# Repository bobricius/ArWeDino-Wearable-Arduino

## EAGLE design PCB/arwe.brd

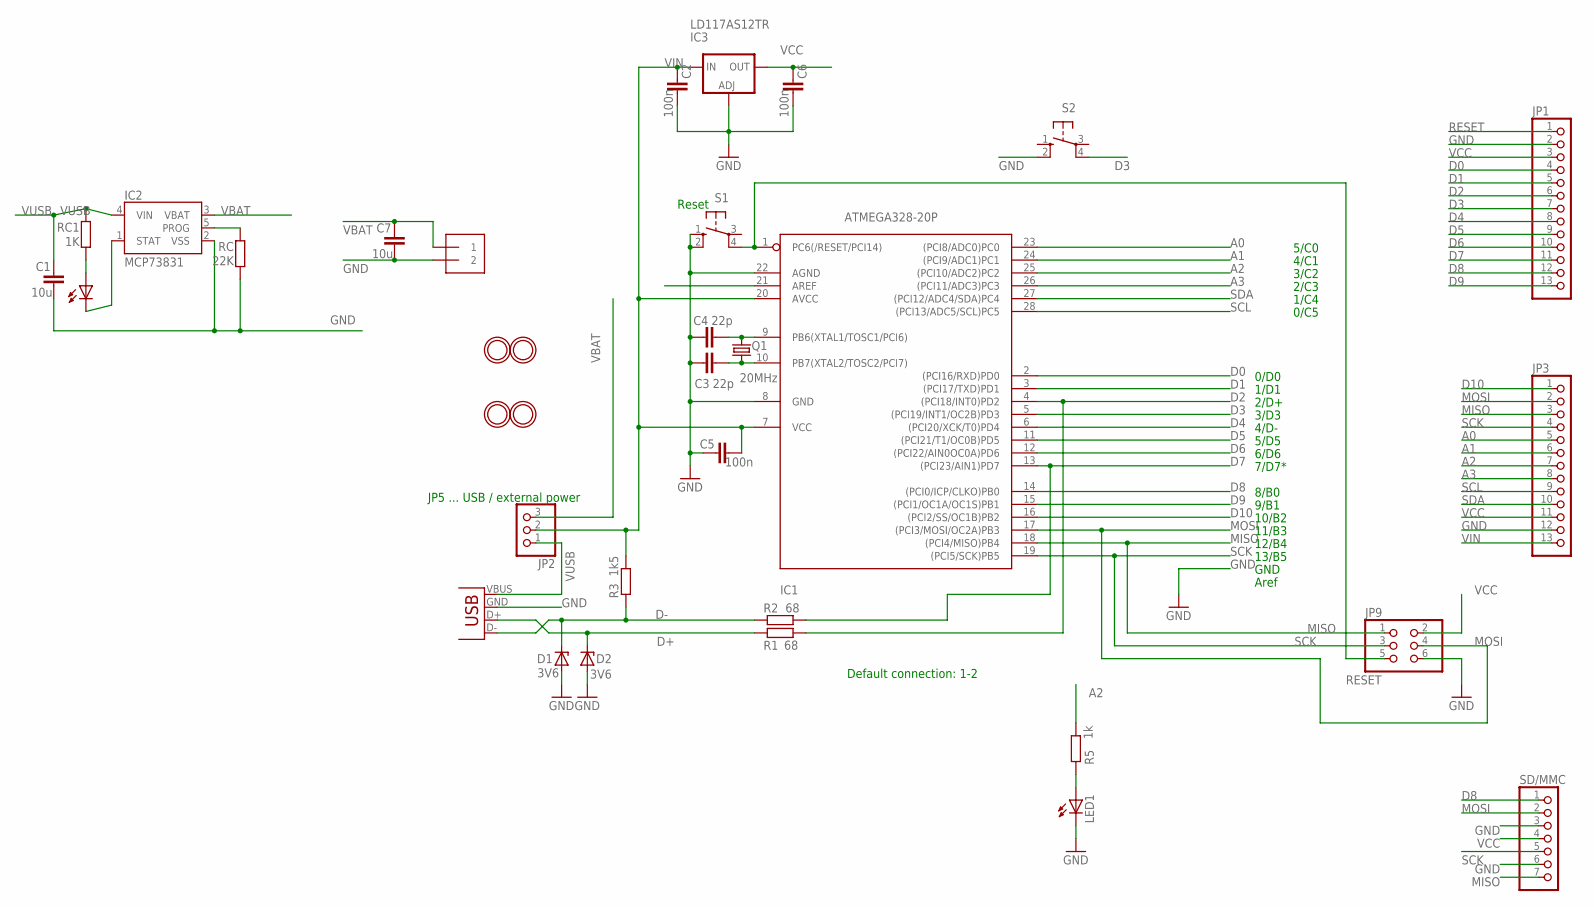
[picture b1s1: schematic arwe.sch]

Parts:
C1, C7: 10u; C0603
C2, C5, C6: 100n; C025-024X044
C3, C4: 22p; C025-024X044
CHG: 0805; CHIPLED_0603
D1, D2: 3V6; ZDIO-5
IC1: ATMEGA328-20P; DIL28-3
IC2: MCP73831; SOT23-5
IC3: LD117AS12TR; SOT223
J1: 1X2-3.5MM
JP1, JP3: PINHD-1X13; 1X13
JP2: PINHD-1X3; 1X03
JP9: PINHD-2X3; 2X03
LED1: LED3MM
Q1: 20MHz; HC49/S
R1, R2: 68; 0204/5
R3: 1k5; 0204/5
R5: 1k; 0204/5
RC: 22K; R0603
RC1: 1K; R0603
S1: 10-XX; B3F-10XX
S2: 10-XX; B3F-10XX; MPN B3F-1000
SD/MMC: PINHD-1X7; 1X07
U$2, U$3, U$4, U$5: MOUNTINGHOLE3.0THIN; MOUNTINGHOLE_3.0_PLATEDTHIN
X1: USB-A-H

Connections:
A0: IC1.23 ((PCI8/ADC0)PC0), JP3.5
A1: IC1.24 ((PCI9/ADC1)PC1), JP3.6
A2: IC1.25 ((PCI10/ADC2)PC2), JP3.7, R5.1
A3: IC1.26 ((PCI11/ADC3)PC3), JP3.8
AREF_RAW: IC1.21 (AREF)
D0: IC1.2 ((PCI16/RXD)PD0), JP1.4
D1: IC1.3 ((PCI17/TXD)PD1), JP1.5
D2: IC1.4 ((PCI18/INT0)PD2), JP1.6, R1.2
D3: IC1.5 ((PCI19/INT1/OC2B)PD3), JP1.7, S2.4 (P1)
D4: IC1.6 ((PCI20/XCK/T0)PD4), JP1.8
D5: IC1.11 ((PCI21/T1/OC0B)PD5), JP1.9
D6: IC1.12 ((PCI22/AIN0OC0A)PD6), JP1.10
D7: IC1.13 ((PCI23/AIN1)PD7), JP1.11, R2.2
D8: IC1.14 ((PCI0/ICP/CLKO)PB0), JP1.12, SD/MMC.1
D9: IC1.15 ((PCI1/OC1A/OC1S)PB1), JP1.13
D10: IC1.16 ((PCI2/SS/OC1B)PB2), JP3.1
D+: D2.C, R1.1, X1.D+ (D-)
D-: D1.C, R2.1, R3.1, X1.D- (D+)
GND: C1.2, C2.2, C3.1, C4.1, C5.1, C6.2, C7.2, D1.A, D2.A, IC1.8 (GND), IC1.22 (AGND), IC2.2 (VSS), IC3.1 (ADJ), J1.2, JP1.2, JP3.12, JP9.6, LED1.K (C), RC.1, S1.1 (S), S1.2 (S1), S2.2 (S1), SD/MMC.3, SD/MMC.6, X1.GND (VBUS)
MISO: IC1.18 ((PCI4/MISO)PB4), JP3.3, JP9.1, SD/MMC.7
MOSI: IC1.17 ((PCI3/MOSI/OC2A)PB3), JP3.2, JP9.4, SD/MMC.2
unnamed: LED1.A, R5.2
unnamed: CHG.A, RC1.1
unnamed: CHG.C, IC2.1 (STAT)
unnamed: IC2.5 (PROG), RC.2
unnamed: C3.2, IC1.10 (PB7(XTAL2/TOSC2/PCI7)), Q1.1
unnamed: C4.2, IC1.9 (PB6(XTAL1/TOSC1/PCI6)), Q1.2
RESET: IC1.1 (PC6(/RESET/PCI14)), JP1.1, JP9.5, S1.4 (P1)
SCK: IC1.19 ((PCI5/SCK)PB5), JP3.4, JP9.3, SD/MMC.5
SCL: IC1.28 ((PCI13/ADC5/SCL)PC5), JP3.9
SDA: IC1.27 ((PCI12/ADC4/SDA)PC4), JP3.10
VBAT: C7.1, IC2.3 (VBAT), J1.1, JP2.3
VCC: C6.1, IC3.4 (OUT), JP1.3, JP3.11, JP9.2, SD/MMC.4
VIN: C2.1, C5.2, IC1.7 (VCC), IC1.20 (AVCC), IC3.3 (IN), JP2.2, JP3.13, R3.2
VUSB: C1.1, IC2.4 (VIN), JP2.1, RC1.2, X1.VBUS (GND)

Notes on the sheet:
JP5 ... USB / external power
Reset
5/C0
4/C1
3/C2
2/C3
1/C4
0/C5
0/D0
1/D1
2/D+
3/D3
4/D-
5/D5
6/D6
7/D7*
8/B0
9/B1
10/B2
11/B3
12/B4
13/B5
GND
Aref
Default connection: 1-2

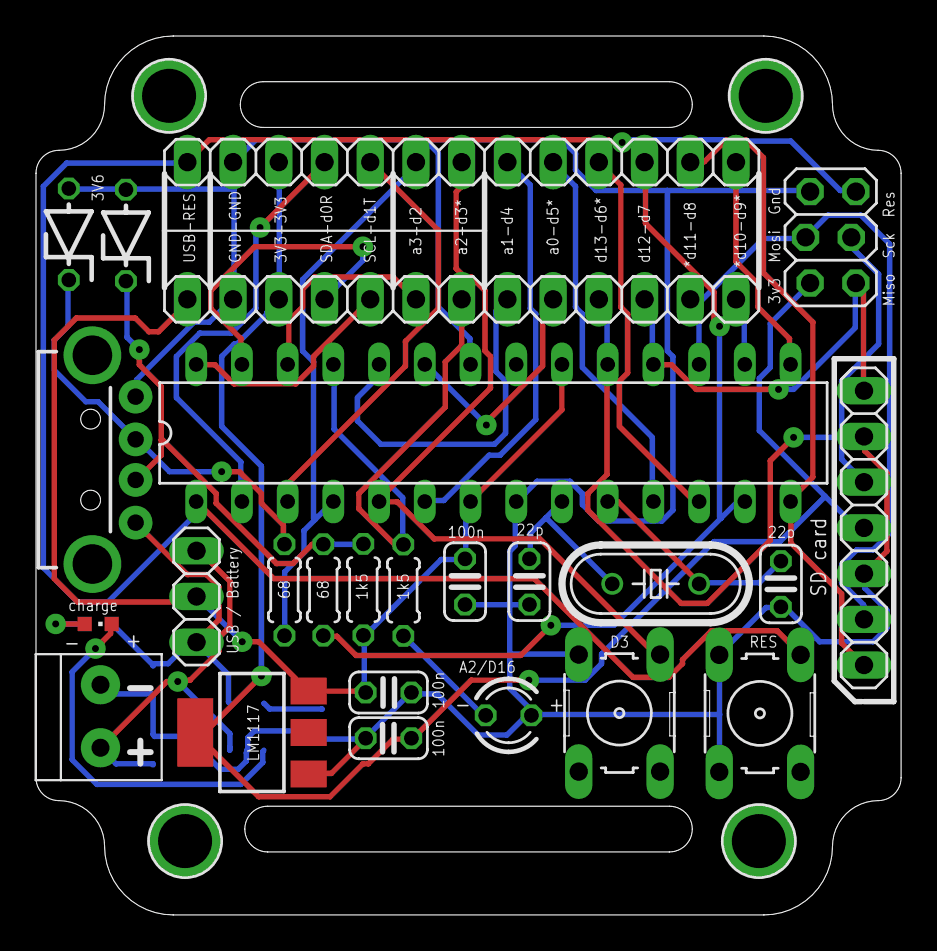
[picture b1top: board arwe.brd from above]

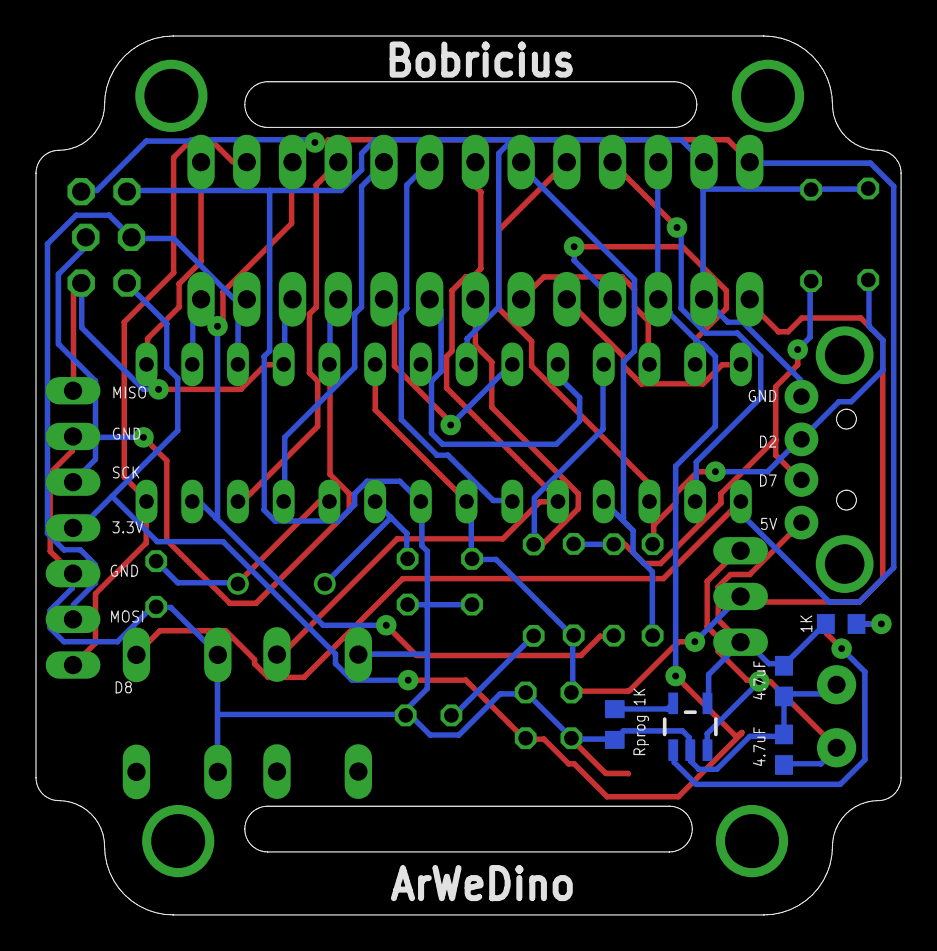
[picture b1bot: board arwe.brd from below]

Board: 2 copper layers, 48.1 x 48.8 mm, 34 parts (5 on the bottom side), 34 nets.

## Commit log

2014-11-12 :space_invader: Added .gitattributes & .gitignore files
2014-11-12 first upload
